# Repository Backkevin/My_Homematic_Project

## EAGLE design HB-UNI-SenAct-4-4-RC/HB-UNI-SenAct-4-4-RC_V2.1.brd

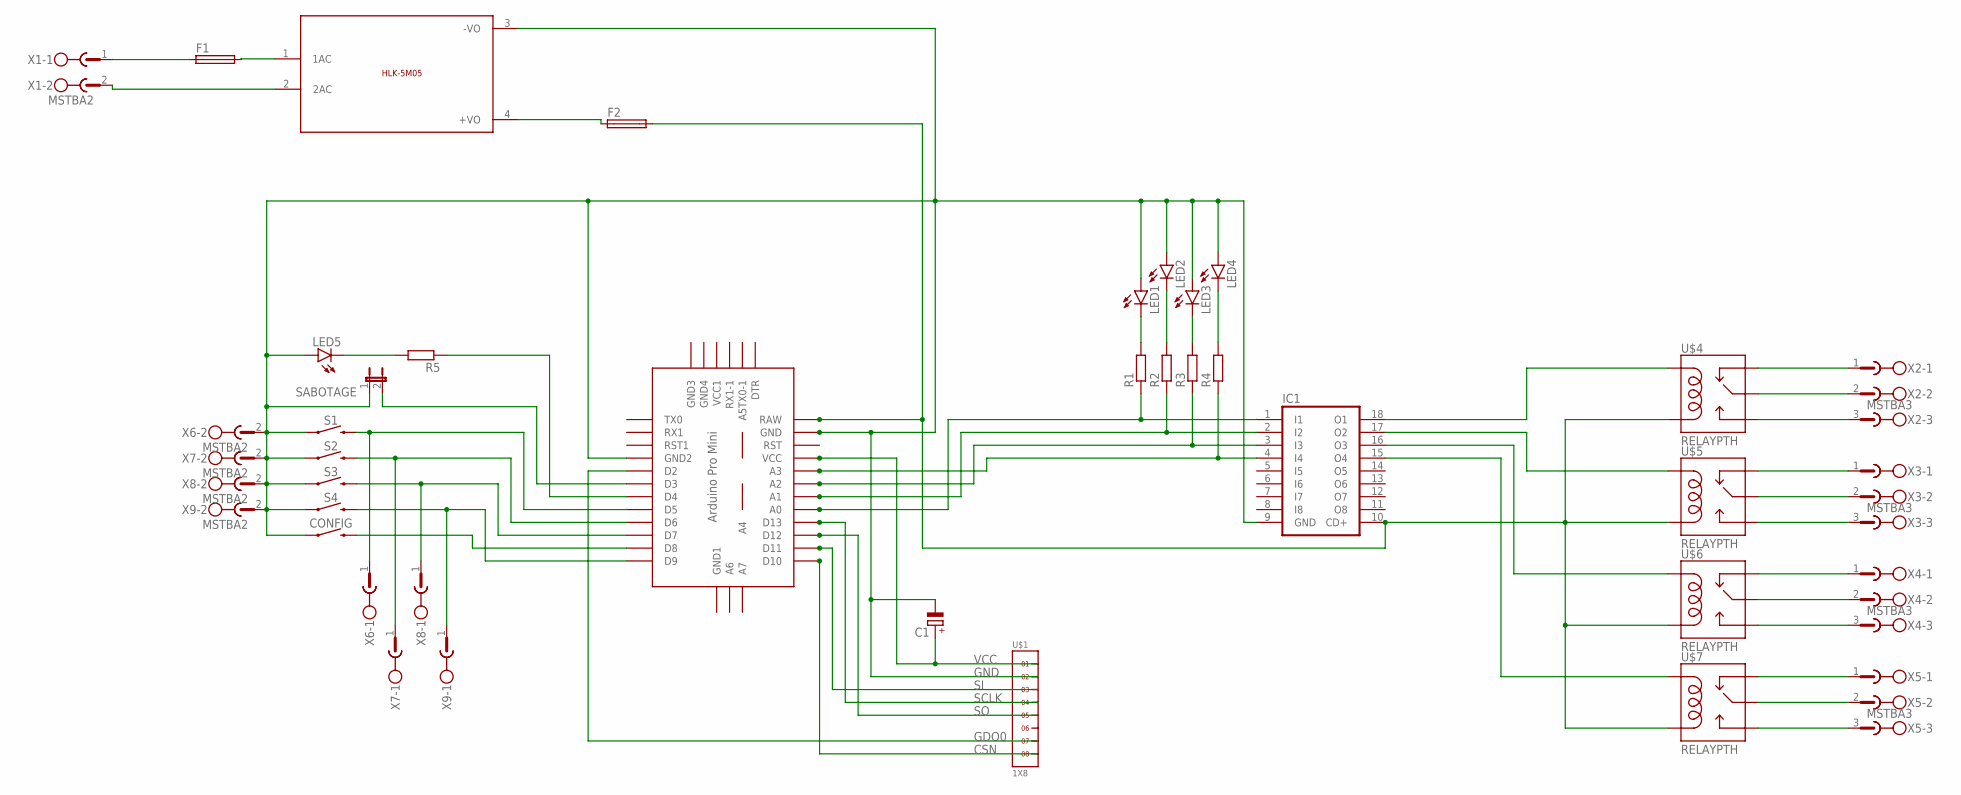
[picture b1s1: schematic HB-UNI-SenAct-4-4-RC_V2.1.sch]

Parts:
C1: CPOL-EUE2.5-5; E2,5-5
CONFIG: MOMENTARY-SWITCH-SPST-PTH-6.0MM-KIT; TACTILE_SWITCH_PTH_6.0MM_KIT
F1, F2: SH22,5A
IC1: ULN2803A; DIL18
LED1, LED2, LED3, LED4, LED5: LED3MM
R1, R2, R3, R4, R5: R-EU_0309/10; 0309/10
S1: MOMENTARY-SWITCH-SPST-PTH-6.0MM; TACTILE_SWITCH_PTH_6.0MM
S2, S3, S4: MOMENTARY-SWITCH-SPST-PTH-6.0MM-KIT; TACTILE_SWITCH_PTH_6.0MM_KIT
SABOTAGE: JP1E; JP1
U$1: 1X8
U$2: ABK-PRO-MINI
U$3: 5VDC/5W; HLK-5M05
U$4, U$5, U$6, U$7: RELAYPTH; SRD-05VDC-SL-C
X1, X6, X7, X8, X9: MSTBA2
X2, X3, X4, X5: MSTBA3

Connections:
CSN: U$1.8, U$2.D10
GDO0: U$1.7, U$2.D2
GND: C1.-, CONFIG.1, IC1.9 (GND), LED1.A, LED2.A, LED3.A, LED4.A, LED5.A, S1.1, S2.1, S3.1, S4.1, SABOTAGE.1, U$1.2, U$2.GND, U$2.GND1 (GND2), U$3.3 (-VO), X6.2, X7.2, X8.2, X9.2
unnamed: IC1.1 (I1), R1.1, U$2.A0
unnamed: IC1.2 (I2), R2.1, U$2.A1
unnamed: IC1.3 (I3), R3.1, U$2.A2
unnamed: IC1.4 (I4), R4.1, U$2.A3
unnamed: LED1.K (C), R1.2
unnamed: LED2.K (C), R2.2
unnamed: LED3.K (C), R3.2
unnamed: LED4.K (C), R4.2
unnamed: F1.1, X1.1
unnamed: F2.1, U$3.4 (+VO)
unnamed: U$3.2 (2AC), X1.2
unnamed: S1.3 (2), U$2.D5, X6.1
unnamed: S2.3 (2), U$2.D6, X7.1
unnamed: S3.3 (2), U$2.D7, X8.1
unnamed: S4.3 (2), U$2.D9, X9.1
unnamed: CONFIG.3 (2), U$2.D8
unnamed: R5.1, U$2.D4
unnamed: LED5.K (C), R5.2
unnamed: F1.2, U$3.1 (1AC)
unnamed: SABOTAGE.2, U$2.D3
unnamed: U$6.SWCLOSED (SWCLOSE), X4.1
unnamed: U$7.SWCOMMON, X5.2
unnamed: U$6.SWOPEN, X4.3
unnamed: F2.2, IC1.10 (CD+), U$2.RAW, U$4.COIL0, U$5.COIL0, U$6.COIL0, U$7.COIL0
unnamed: U$7.SWCLOSED (SWCLOSE), X5.1
unnamed: U$6.SWCOMMON, X4.2
unnamed: U$7.SWOPEN, X5.3
unnamed: U$5.SWOPEN, X3.3
unnamed: U$5.SWCOMMON, X3.2
unnamed: U$5.SWCLOSED (SWCLOSE), X3.1
unnamed: U$4.SWOPEN, X2.3
unnamed: U$4.SWCOMMON, X2.2
unnamed: U$4.SWCLOSED (SWCLOSE), X2.1
unnamed: IC1.18 (O1), U$4.COIL1
unnamed: IC1.17 (O2), U$5.COIL1
unnamed: IC1.16 (O3), U$6.COIL1
unnamed: IC1.15 (O4), U$7.COIL1
SCLK: U$1.4, U$2.D13
SI: U$1.3, U$2.D11
SO: U$1.5, U$2.D12
VCC: C1.+, U$1.1, U$2.VCC

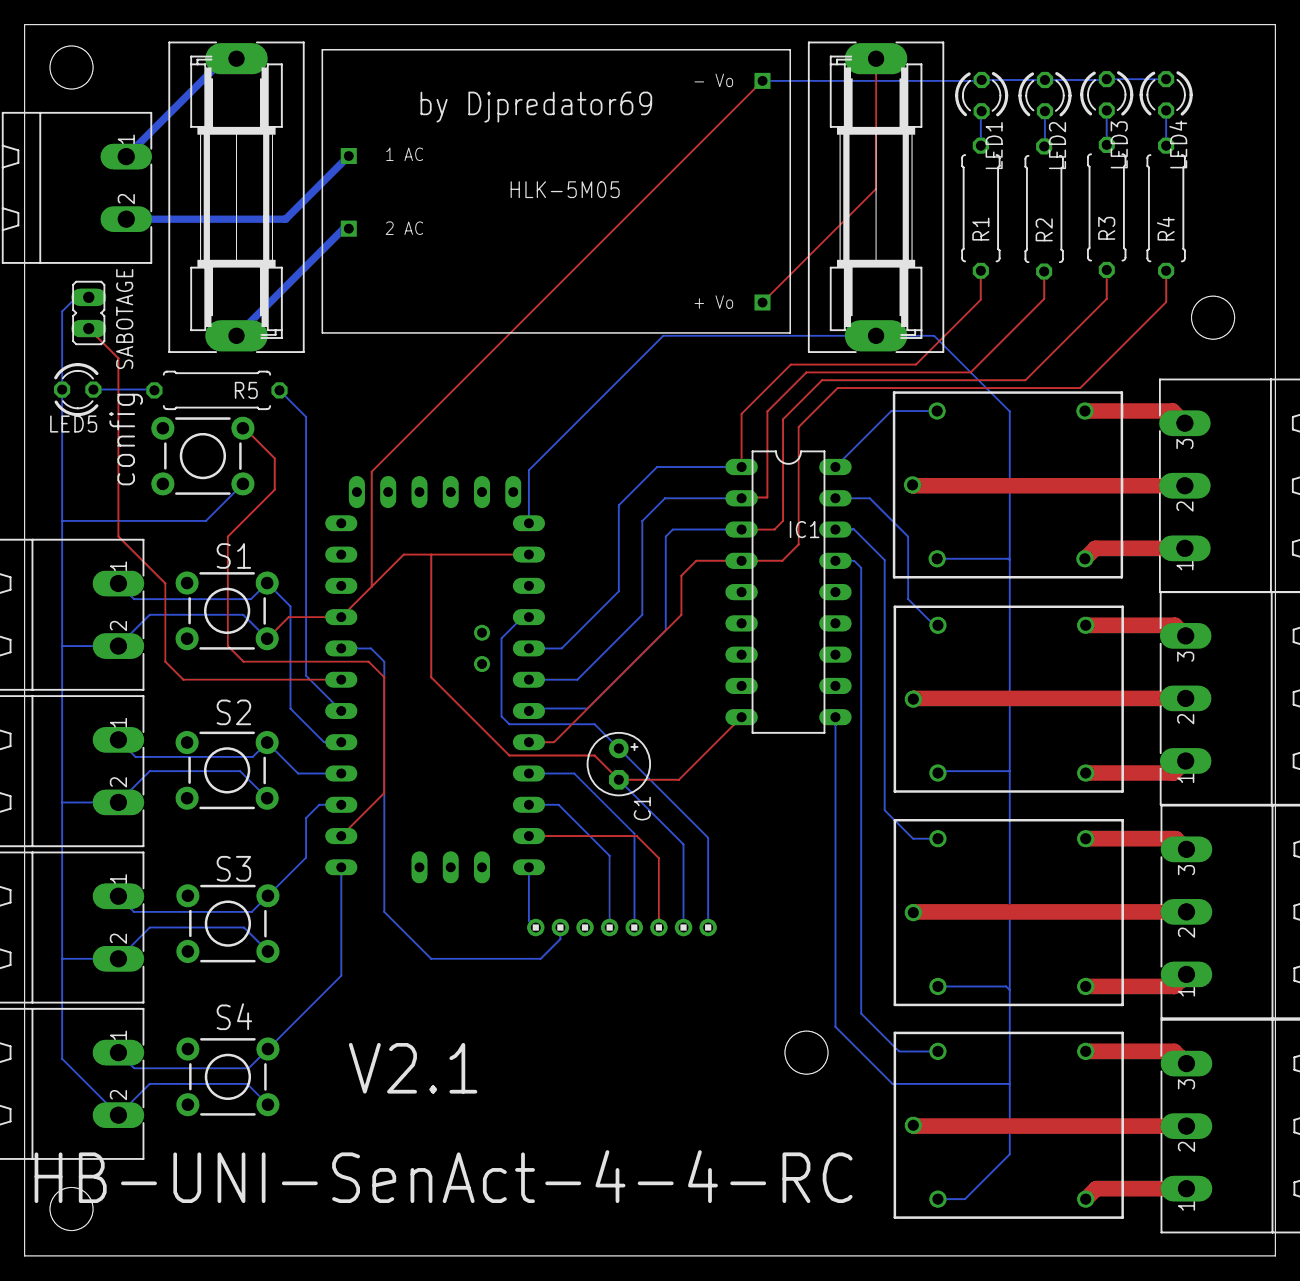
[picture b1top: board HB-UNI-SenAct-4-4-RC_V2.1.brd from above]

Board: 2 copper layers, 101.6 x 100.0 mm, 36 parts (0 on the bottom side), 44 nets.

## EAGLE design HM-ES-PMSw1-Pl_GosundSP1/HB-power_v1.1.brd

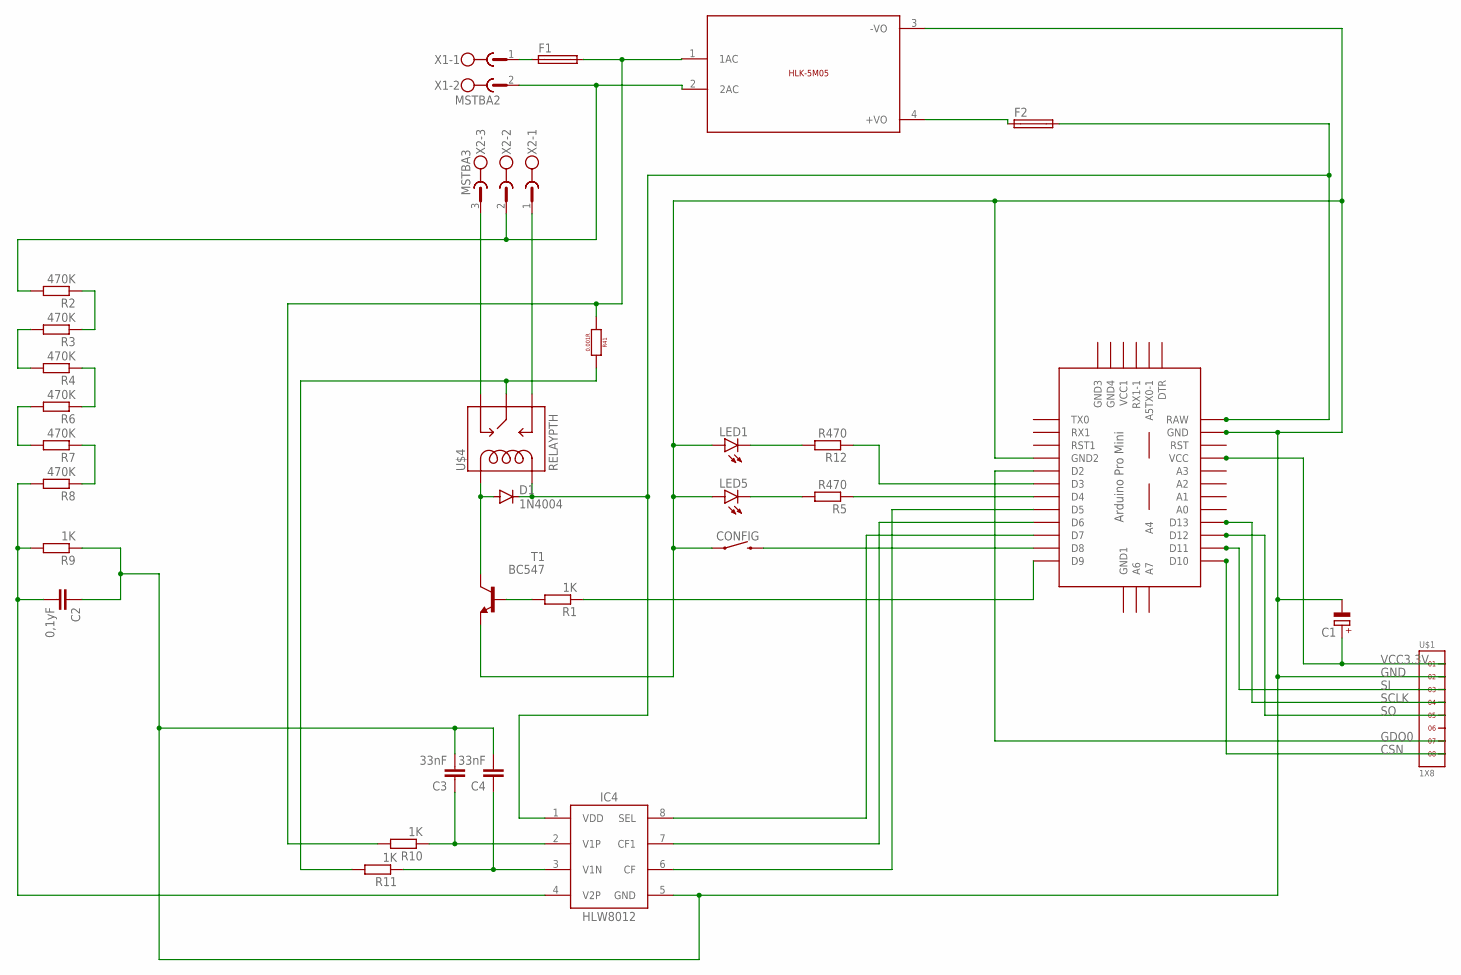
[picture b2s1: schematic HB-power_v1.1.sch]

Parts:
C1: CPOL-EUE2.5-5; E2,5-5
C2: 0,1yF; C050-024X044
C3, C4: 33nF; C050-024X044
CONFIG: MOMENTARY-SWITCH-SPST-PTH-6.0MM-KIT; TACTILE_SWITCH_PTH_6.0MM_KIT
D1: 1N4004; DO41-10
F1, F2: SH22,5A
IC4: HLW8012; SOP8
LED1, LED5: LED3MM
R1, R9, R10, R11: 1K; 0309/10
R2, R3, R4, R6, R7, R8: 470K; 0309/10
R5, R12: R470; 0309/10
R41: 0.001R; 2512
T1: BC547; TO92
U$1: 1X8
U$2: ABK-PRO-MINI
U$3: 5VDC/5W; HLK-5M05
U$4: RELAYPTH; SRD-05VDC-SL-C
X1: MSTBA2
X2: MSTBA3

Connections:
CSN: U$1.8, U$2.D10
GDO0: U$1.7, U$2.D2
GND: C1.-, C2.1, C3.2, C4.2, CONFIG.1, IC4.5 (GND), LED1.A, LED5.A, R9.1, T1.1 (E), U$1.2, U$2.GND, U$2.GND1 (GND2), U$3.3 (-VO)
L: F1.1, X1.1
L1: F1.2, R10.2, R41.1, U$3.1 (1AC)
L2: R11.2, R41.2, U$4.SWCOMMON
N: R2.2, U$3.2 (2AC), X1.2, X2.2
unnamed: D1.A, T1.3 (C), U$4.COIL1
unnamed: R1.2, T1.2 (B)
unnamed: LED1.K (C), R12.2
unnamed: R1.1, U$2.D9
unnamed: R12.1, U$2.D3
unnamed: IC4.8 (SEL), U$2.D7
unnamed: IC4.7 (CF1), U$2.D6
unnamed: IC4.6 (CF), U$2.D5
unnamed: F2.1, U$3.4 (+VO)
unnamed: U$4.SWCLOSED (SWCLOSE), X2.3
unnamed: U$4.SWOPEN, X2.1
unnamed: R2.1, R3.1
unnamed: R4.1, R6.1
unnamed: R7.1, R8.1
unnamed: CONFIG.3 (2), U$2.D8
unnamed: R5.1, U$2.D4
unnamed: LED5.K (C), R5.2
unnamed: R3.2, R4.2
unnamed: R6.2, R7.2
unnamed: C2.2, IC4.4 (V2P), R8.2, R9.2
unnamed: C3.1, IC4.2 (V1P), R10.1
unnamed: C4.1, IC4.3 (V1N), R11.1
SCLK: U$1.4, U$2.D13
SI: U$1.3, U$2.D11
SO: U$1.5, U$2.D12
VCC3.3V: C1.+, U$1.1, U$2.VCC
VCC5V: D1.C, F2.2, IC4.1 (VDD), U$2.RAW, U$4.COIL0

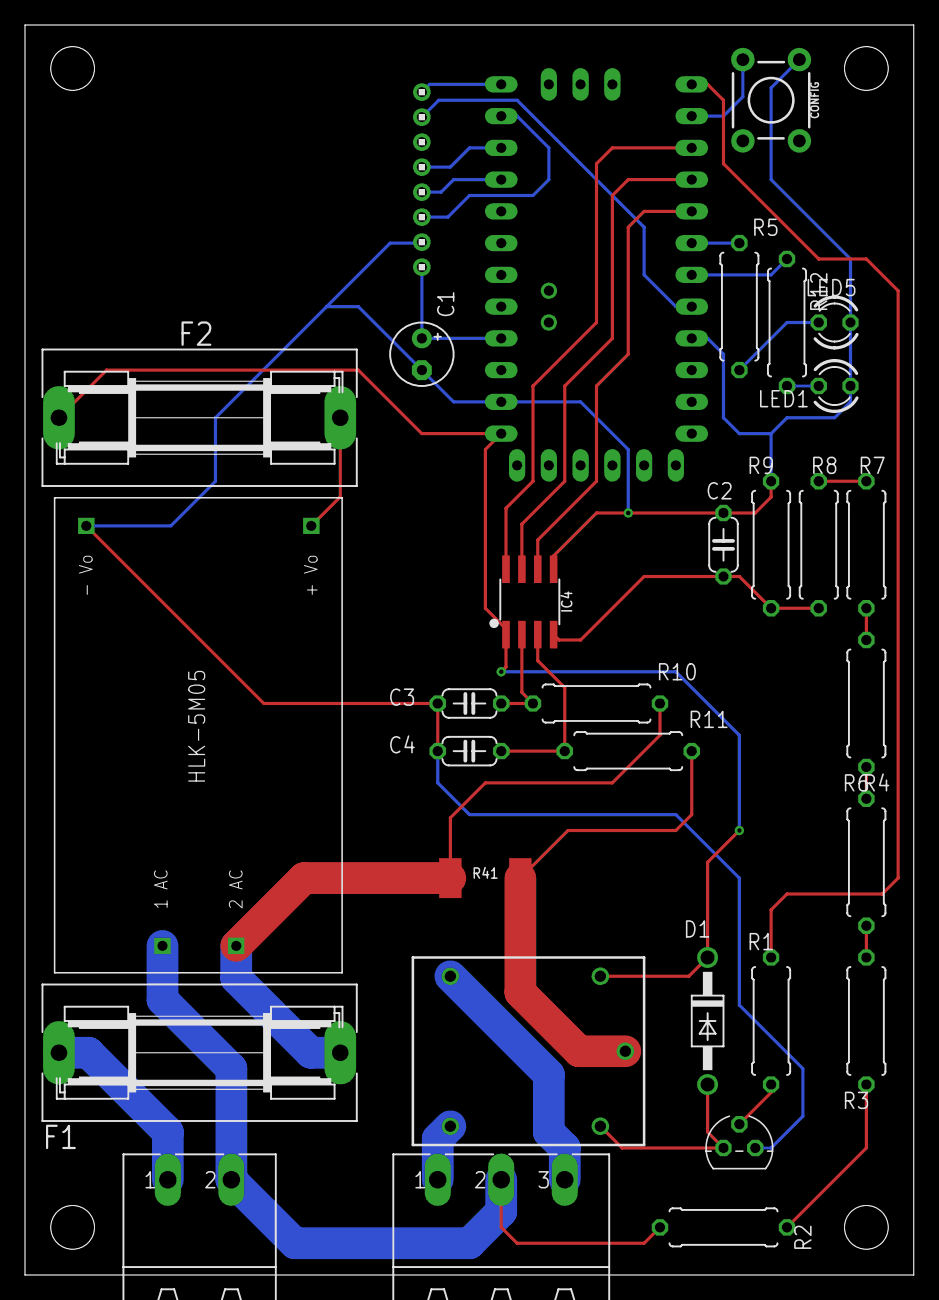
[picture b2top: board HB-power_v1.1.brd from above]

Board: 2 copper layers, 71.1 x 100.0 mm, 31 parts (0 on the bottom side), 34 nets.

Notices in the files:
parts and their libraries:
SparkFun-Switches: Licensing: Creative Commons ShareAlike 4.0 International - https://creativecommons.org/licenses/by-sa/4.0
